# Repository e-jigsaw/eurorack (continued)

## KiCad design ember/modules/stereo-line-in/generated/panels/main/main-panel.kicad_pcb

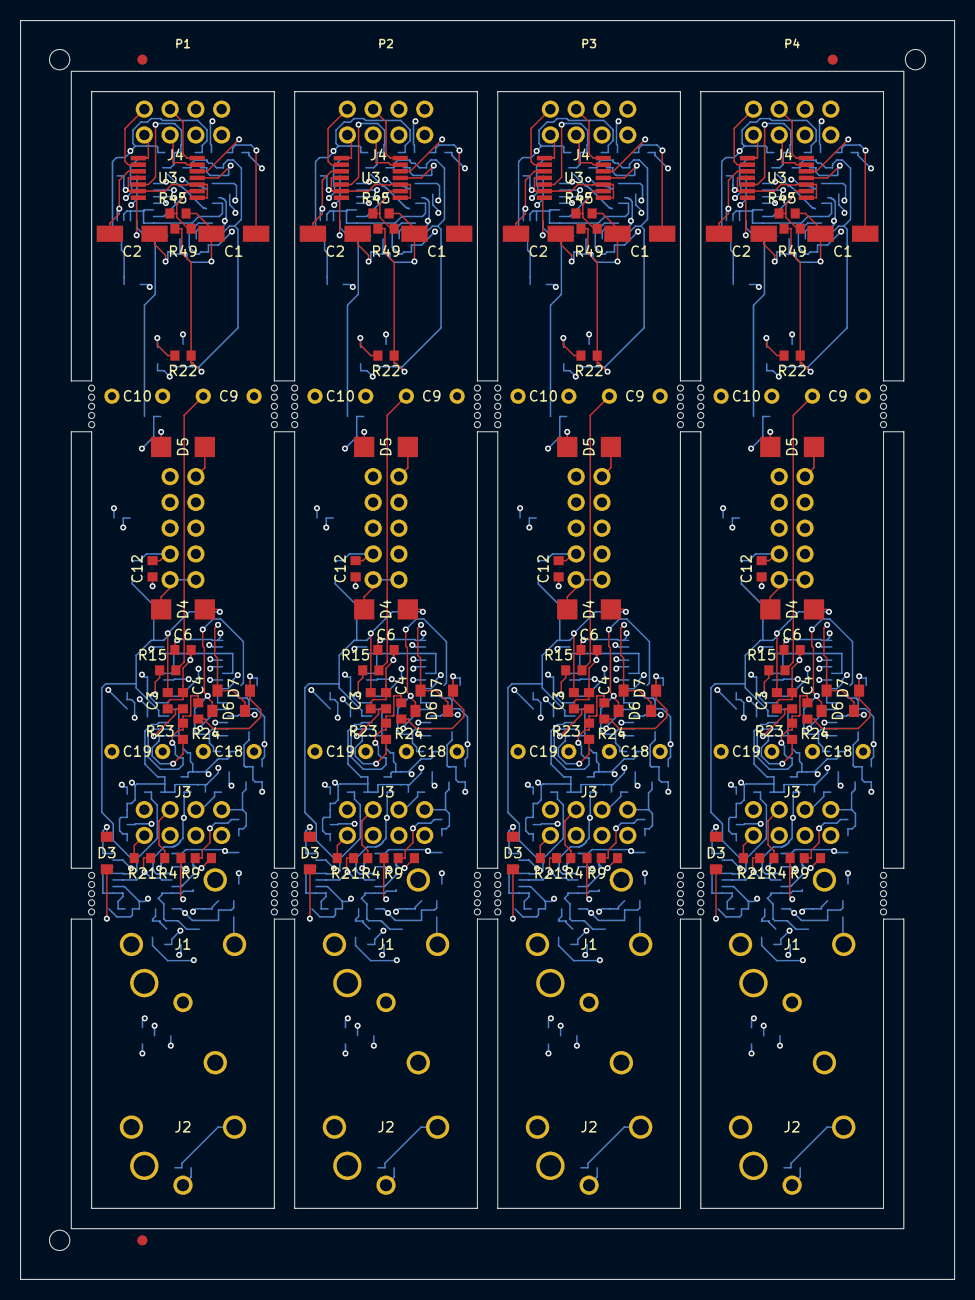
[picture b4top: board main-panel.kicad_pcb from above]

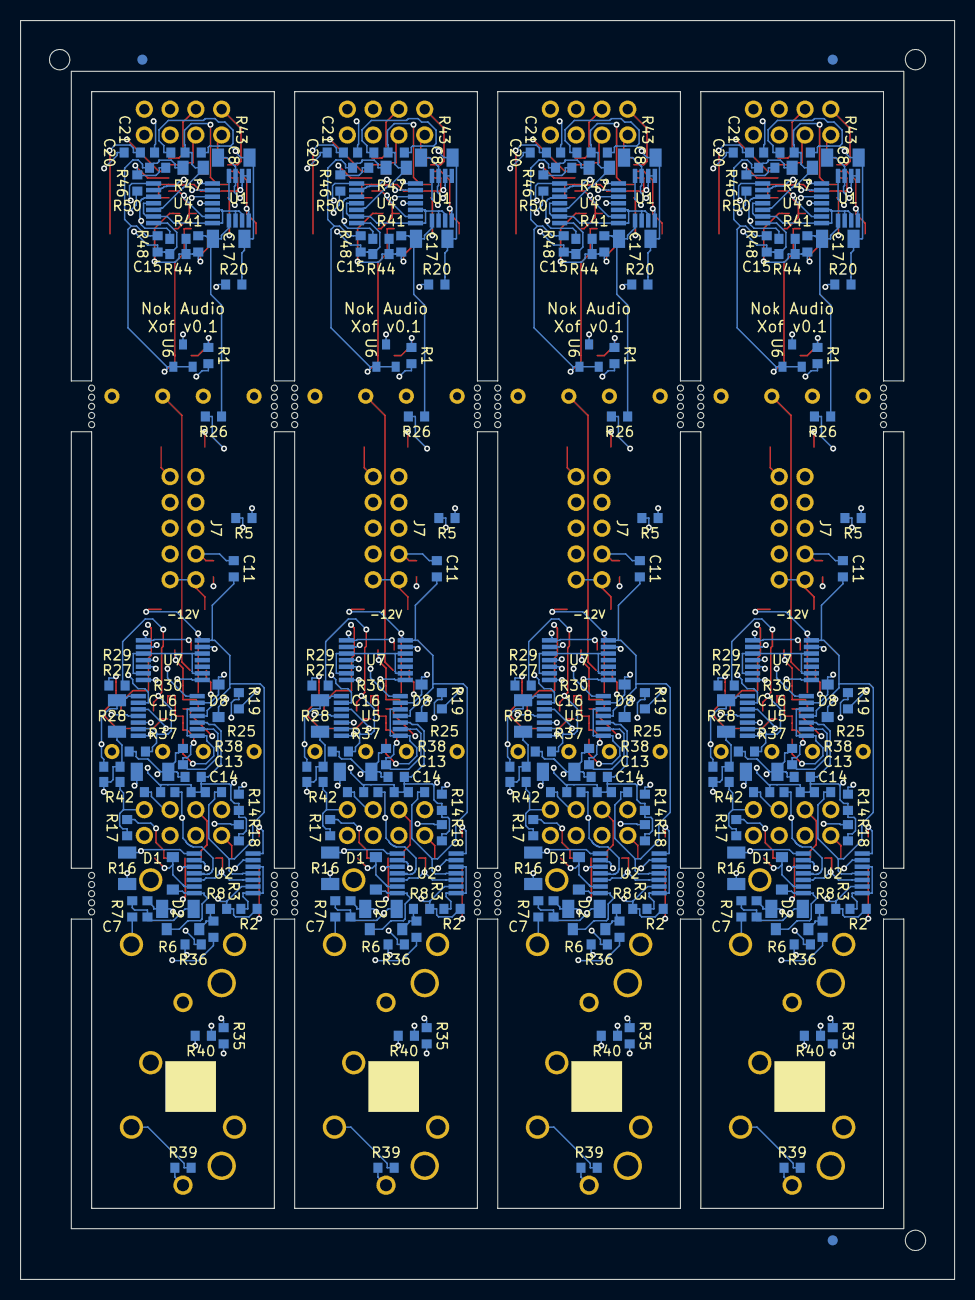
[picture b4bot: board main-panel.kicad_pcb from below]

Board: 4 copper layers, 92.0 x 124.0 mm, 417 parts (215 on the bottom side), 236 nets.

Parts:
FIDB1, FIDB2, FIDB3: Panel_Fiducial
FIDF1, FIDF2, FIDF3: Panel_Fiducial
MB1, MB2, MB3, MB4, MB5, MB6, MB7, MB8, MB9, MB10, MB11, MB12, MB13, MB14, MB15, MB16, MB17, MB18, MB19, MB20, MB21, MB22, MB23, MB24, MB25, MB26, MB27, MB28, MB29, MB30, MB31, MB32, MB33, MB34, MB35, MB36, MB37, MB38, MB39, MB40, MB41, MB42, MB43, MB44, MB45, MB46, MB47, MB48, MB49, MB50, MB51, MB52, MB53, MB54, MB55, MB56, MB57, MB58, MB59, MB60, MB61, MB62, MB63, MB64, MB65, MB66, MB67, MB68, MB69, MB70, MB71, MB72, MB73, MB74, MB75, MB76, MB77, MB78, MB79, MB80: Panel_NPTH
P1_C_BULK_N, P1_C_BULK_P, P2_C_BULK_N, P2_C_BULK_P, P3_C_BULK_N, P3_C_BULK_P, P4_C_BULK_N, P4_C_BULK_P: RVT1E220M0505; SMD,D5xL5.4mm
P1_C_ENV_N, P1_C_ENV_P, P1_C_L_CMP, P1_C_L_VN, P1_C_L_VP, P1_C_RX_N, P1_C_RX_P, P1_C_R_CMP, P1_C_R_VN, P1_C_R_VP, P2_C_ENV_N, P2_C_ENV_P, P2_C_L_CMP, P2_C_L_VN, P2_C_L_VP, P2_C_RX_N, P2_C_RX_P, P2_C_R_CMP, P2_C_R_VN, P2_C_R_VP, P3_C_ENV_N, P3_C_ENV_P, P3_C_L_CMP, P3_C_L_VN, P3_C_L_VP, P3_C_RX_N, P3_C_RX_P, P3_C_R_CMP, P3_C_R_VN, P3_C_R_VP, P4_C_ENV_N, P4_C_ENV_P, P4_C_L_CMP, P4_C_L_VN, P4_C_L_VP, P4_C_RX_N, P4_C_RX_P, P4_C_R_CMP, P4_C_R_VN, P4_C_R_VP: CC0603KRX7R9BB104; 0603
P1_C_L_GAIN_F, P1_C_R_GAIN_F, P2_C_L_GAIN_F, P2_C_R_GAIN_F, P3_C_L_GAIN_F, P3_C_R_GAIN_F, P4_C_L_GAIN_F, P4_C_R_GAIN_F: CL10C100JB8NNNC; 0603
P1_C_L_HOLD, P1_C_R_HOLD, P2_C_L_HOLD, P2_C_R_HOLD, P3_C_L_HOLD, P3_C_R_HOLD, P4_C_L_HOLD, P4_C_R_HOLD: GRM31C5C1H104JA01L; 1206
P1_C_L_N_AC, P1_C_L_P_AC, P1_C_R_N_AC, P1_C_R_P_AC, P2_C_L_N_AC, P2_C_L_P_AC, P2_C_R_N_AC, P2_C_R_P_AC, P3_C_L_N_AC, P3_C_L_P_AC, P3_C_R_N_AC, P3_C_R_P_AC, P4_C_L_N_AC, P4_C_L_P_AC, P4_C_R_N_AC, P4_C_R_P_AC: MKS2C041001F00JSSD; WIMA
P1_D_L_HALF_CLAMP, P1_D_L_HALF_RECT, P1_D_L_PEAK, P1_D_R_HALF_CLAMP, P1_D_R_HALF_RECT, P1_D_R_PEAK, P2_D_L_HALF_CLAMP, P2_D_L_HALF_RECT, P2_D_L_PEAK, P2_D_R_HALF_CLAMP, P2_D_R_HALF_RECT, P2_D_R_PEAK, P3_D_L_HALF_CLAMP, P3_D_L_HALF_RECT, P3_D_L_PEAK, P3_D_R_HALF_CLAMP, P3_D_R_HALF_RECT, P3_D_R_PEAK, P4_D_L_HALF_CLAMP, P4_D_L_HALF_RECT, P4_D_L_PEAK, P4_D_R_HALF_CLAMP, P4_D_R_HALF_RECT, P4_D_R_PEAK: 1N4148W; SOD-123
P1_D_PWR_N, P1_D_PWR_P, P2_D_PWR_N, P2_D_PWR_P, P3_D_PWR_N, P3_D_PWR_P, P4_D_PWR_N, P4_D_PWR_P: SS14; SMA(DO-214AC)
P1_J_IN_L, P1_J_IN_R, P2_J_IN_L, P2_J_IN_R, P3_J_IN_L, P3_J_IN_R, P4_J_IN_L, P4_J_IN_R: NJ3FD-V
P1_J_LINK_BOTTOM, P1_J_LINK_TOP, P2_J_LINK_BOTTOM, P2_J_LINK_TOP, P3_J_LINK_BOTTOM, P3_J_LINK_TOP, P4_J_LINK_BOTTOM, P4_J_LINK_TOP: SSW-104-01-F-D; SSW-2x4
P1_J_PWR, P2_J_PWR, P3_J_PWR, P4_J_PWR: DC3-2.54-10PAS; DC3
P1_R_LED_SUPPLY, P2_R_LED_SUPPLY, P3_R_LED_SUPPLY, P4_R_LED_SUPPLY: 0603WAF470JT5E; 0603
P1_R_L_ABS_FB, P1_R_R_ABS_FB, P2_R_L_ABS_FB, P2_R_R_ABS_FB, P3_R_L_ABS_FB, P3_R_R_ABS_FB, P4_R_L_ABS_FB, P4_R_R_ABS_FB: RT0603BRD0720KL; 0603
P1_R_L_ABS_HALF, P1_R_R_ABS_HALF, P2_R_L_ABS_HALF, P2_R_R_ABS_HALF, P3_R_L_ABS_HALF, P3_R_R_ABS_HALF, P4_R_L_ABS_HALF, P4_R_R_ABS_HALF: RT0603BRD0750KL; 0603
P1_R_L_ABS_RAW, P1_R_L_HALF_FB, P1_R_L_HALF_IN, P1_R_R_ABS_RAW, P1_R_R_HALF_FB, P1_R_R_HALF_IN, P2_R_L_ABS_RAW, P2_R_L_HALF_FB, P2_R_L_HALF_IN, P2_R_R_ABS_RAW, P2_R_R_HALF_FB, P2_R_R_HALF_IN, P3_R_L_ABS_RAW, P3_R_L_HALF_FB, P3_R_L_HALF_IN, P3_R_R_ABS_RAW, P3_R_R_HALF_FB, P3_R_R_HALF_IN, P4_R_L_ABS_RAW, P4_R_L_HALF_FB, P4_R_L_HALF_IN, P4_R_R_ABS_RAW, P4_R_R_HALF_FB, P4_R_R_HALF_IN: RT0603BRD07100KL; 0603
P1_R_L_ATTACK, P1_R_R_ATTACK, P2_R_L_ATTACK, P2_R_R_ATTACK, P3_R_L_ATTACK, P3_R_R_ATTACK, P4_R_L_ATTACK, P4_R_R_ATTACK: 0603WAF1001T5E; 0603
P1_R_L_GAIN_F, P1_R_R_GAIN_F, P2_R_L_GAIN_F, P2_R_R_GAIN_F, P3_R_L_GAIN_F, P3_R_R_GAIN_F, P4_R_L_GAIN_F, P4_R_R_GAIN_F: RT1206BRE0790KL; 1206
P1_R_L_GAIN_G, P1_R_R_GAIN_G, P1_R_TH_BOTTOM_1, P1_R_TH_BOTTOM_2, P1_R_TH_BOTTOM_3, P1_R_TH_BOTTOM_4, P2_R_L_GAIN_G, P2_R_R_GAIN_G, P2_R_TH_BOTTOM_1, P2_R_TH_BOTTOM_2, P2_R_TH_BOTTOM_3, P2_R_TH_BOTTOM_4, P3_R_L_GAIN_G, P3_R_R_GAIN_G, P3_R_TH_BOTTOM_1, P3_R_TH_BOTTOM_2, P3_R_TH_BOTTOM_3, P3_R_TH_BOTTOM_4, P4_R_L_GAIN_G, P4_R_R_GAIN_G, P4_R_TH_BOTTOM_1, P4_R_TH_BOTTOM_2, P4_R_TH_BOTTOM_3, P4_R_TH_BOTTOM_4: RT0603BRD0710KL; 0603
P1_R_L_N_BLEED, P1_R_L_OUT_BLEED, P1_R_L_P_BLEED, P1_R_L_RELEASE, P1_R_L_WIPER_FAIL, P1_R_R_N_BLEED, P1_R_R_OUT_BLEED, P1_R_R_P_BLEED, P1_R_R_RELEASE, P1_R_R_WIPER_FAIL, P2_R_L_N_BLEED, P2_R_L_OUT_BLEED, P2_R_L_P_BLEED, P2_R_L_RELEASE, P2_R_L_WIPER_FAIL, P2_R_R_N_BLEED, P2_R_R_OUT_BLEED, P2_R_R_P_BLEED, P2_R_R_RELEASE, P2_R_R_WIPER_FAIL, P3_R_L_N_BLEED, P3_R_L_OUT_BLEED, P3_R_L_P_BLEED, P3_R_L_RELEASE, P3_R_L_WIPER_FAIL, P3_R_R_N_BLEED, P3_R_R_OUT_BLEED, P3_R_R_P_BLEED, P3_R_R_RELEASE, P3_R_R_WIPER_FAIL, P4_R_L_N_BLEED, P4_R_L_OUT_BLEED, P4_R_L_P_BLEED, P4_R_L_RELEASE, P4_R_L_WIPER_FAIL, P4_R_R_N_BLEED, P4_R_R_OUT_BLEED, P4_R_R_P_BLEED, P4_R_R_RELEASE, P4_R_R_WIPER_FAIL: 0603WAF1004T5E; 0603
P1_R_L_N_SERIES, P1_R_L_P_SERIES, P1_R_R_N_SERIES, P1_R_R_P_SERIES, P2_R_L_N_SERIES, P2_R_L_P_SERIES, P2_R_R_N_SERIES, P2_R_R_P_SERIES, P3_R_L_N_SERIES, P3_R_L_P_SERIES, P3_R_R_N_SERIES, P3_R_R_P_SERIES, P4_R_L_N_SERIES, P4_R_L_P_SERIES, P4_R_R_N_SERIES, P4_R_R_P_SERIES: RT0603BRD071KL; 0603
P1_R_L_OUT, P1_R_R_OUT, P2_R_L_OUT, P2_R_R_OUT, P3_R_L_OUT, P3_R_R_OUT, P4_R_L_OUT, P4_R_R_OUT: HP06W2F1000T5E; 1206
P1_R_REFERENCE, P2_R_REFERENCE, P3_R_REFERENCE, P4_R_REFERENCE: 0603WAF2201T5E; 0603
P1_R_TH_TOP_1, P2_R_TH_TOP_1, P3_R_TH_TOP_1, P4_R_TH_TOP_1: RT0805BRD07240KL; 0805
P1_R_TH_TOP_2, P2_R_TH_TOP_2, P3_R_TH_TOP_2, P4_R_TH_TOP_2: RT0603BRD0752K3L; 0603
P1_R_TH_TOP_3, P2_R_TH_TOP_3, P3_R_TH_TOP_3, P4_R_TH_TOP_3: RT0603BRD0715KL; 0603
P1_R_TH_TOP_4, P2_R_TH_TOP_4, P3_R_TH_TOP_4, P4_R_TH_TOP_4: RT0603BRD075K62L; 0603
P1_U_ENV, P2_U_ENV, P3_U_ENV, P4_U_ENV: OPA1678IDGKR; VSSOP-8
P1_U_L, P1_U_R, P2_U_L, P2_U_R, P3_U_L, P3_U_R, P4_U_L, P4_U_R: OPA1679IPWR; TSSOP-14
P1_U_METER_L, P1_U_METER_R, P2_U_METER_L, P2_U_METER_R, P3_U_METER_L, P3_U_METER_R, P4_U_METER_L, P4_U_METER_R: LM339BIPWR; TSSOP-14
P1_U_REF, P2_U_REF, P3_U_REF, P4_U_REF: TL431BIDBZR; SOT-23-3
P1_U_RX, P2_U_RX, P3_U_RX, P4_U_RX: INA1650IPWR; TSSOP-14
TOOL1, TOOL2, TOOL3: Panel_NPTH

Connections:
P1_GND: P1_C_BULK_N.1, P1_C_BULK_P.2, P1_C_ENV_N.1, P1_C_ENV_P.2, P1_C_L_CMP.2, P1_C_L_HOLD.2, P1_C_L_VN.1, P1_C_L_VP.2, P1_C_RX_N.1, P1_C_RX_P.2, P1_C_R_CMP.2, P1_C_R_HOLD.2, P1_C_R_VN.1, P1_C_R_VP.2, P1_J_IN_L.3, P1_J_IN_R.3, P1_J_LINK_BOTTOM.7, P1_J_PWR.3, P1_J_PWR.4, P1_J_PWR.5, P1_J_PWR.6, P1_J_PWR.7, P1_J_PWR.8, P1_R_L_GAIN_G.2, P1_R_L_N_BLEED.2, P1_R_L_OUT_BLEED.2, P1_R_L_P_BLEED.2, P1_R_L_RELEASE.2, P1_R_L_WIPER_FAIL.2, P1_R_R_GAIN_G.2, P1_R_R_N_BLEED.2, P1_R_R_OUT_BLEED.2, P1_R_R_P_BLEED.2, P1_R_R_RELEASE.2, P1_R_R_WIPER_FAIL.2, P1_R_TH_BOTTOM_1.2, P1_R_TH_BOTTOM_2.2, P1_R_TH_BOTTOM_3.2, P1_R_TH_BOTTOM_4.2, P1_U_L.5, P1_U_L.10, P1_U_METER_L.12, P1_U_METER_R.12, P1_U_R.5, P1_U_R.10, P1_U_REF.3, P1_U_RX.3, P1_U_RX.6, P1_U_RX.9, P1_U_RX.12
P1_L_ABS: P1_R_L_ABS_FB.1, P1_U_L.8, P1_U_L.12
P1_L_ABS_SUM: P1_R_L_ABS_FB.2, P1_R_L_ABS_HALF.2, P1_R_L_ABS_RAW.2, P1_U_L.9
P1_L_DRIVE: P1_C_L_GAIN_F.1, P1_R_L_GAIN_F.1, P1_R_L_OUT.1, P1_U_L.1
P1_L_ENV: P1_C_L_HOLD.1, P1_R_L_ATTACK.2, P1_R_L_RELEASE.1, P1_U_ENV.3
P1_L_ENV_BUF: P1_U_ENV.1, P1_U_ENV.2, P1_U_METER_L.4, P1_U_METER_L.6, P1_U_METER_L.8, P1_U_METER_L.10
P1_L_GAIN_FB: P1_C_L_GAIN_F.2, P1_R_L_GAIN_F.2, P1_R_L_GAIN_G.1, P1_U_L.2
P1_L_HALF: P1_D_L_HALF_RECT.2, P1_R_L_ABS_HALF.1, P1_R_L_HALF_FB.1
P1_L_HALF_DRIVE: P1_D_L_HALF_CLAMP.2, P1_D_L_HALF_RECT.1, P1_U_L.7
P1_L_HALF_SUM: P1_D_L_HALF_CLAMP.1, P1_R_L_HALF_FB.2, P1_R_L_HALF_IN.2, P1_U_L.6
P1_L_LED_1_K: P1_J_LINK_TOP.1, P1_U_METER_L.2
P1_L_LED_2_K: P1_J_LINK_TOP.2, P1_U_METER_L.1
P1_L_LED_3_K: P1_J_LINK_TOP.3, P1_U_METER_L.14
P1_L_LED_4_K: P1_J_LINK_TOP.4, P1_U_METER_L.13
P1_L_N_SERIES: P1_C_L_N_AC.1, P1_R_L_N_SERIES.2
P1_L_OUT: P1_J_LINK_BOTTOM.3, P1_R_L_ABS_RAW.1, P1_R_L_HALF_IN.1, P1_R_L_OUT.2, P1_R_L_OUT_BLEED.1
P1_L_PEAK_DRIVE: P1_D_L_PEAK.2, P1_U_L.14
P1_L_PEAK_FOLLOW: P1_D_L_PEAK.1, P1_R_L_ATTACK.1, P1_U_L.13
P1_L_P_SERIES: P1_C_L_P_AC.1, P1_R_L_P_SERIES.2
P1_L_RING: P1_J_IN_L.2, P1_R_L_N_BLEED.1, P1_R_L_N_SERIES.1
P1_L_RX_N: P1_C_L_N_AC.2, P1_U_RX.4
P1_L_RX_OUT: P1_J_LINK_BOTTOM.1, P1_U_RX.13
P1_L_RX_P: P1_C_L_P_AC.2, P1_U_RX.2
P1_L_TIP: P1_J_IN_L.1, P1_R_L_P_BLEED.1, P1_R_L_P_SERIES.1
P1_L_WIPER: P1_J_LINK_BOTTOM.2, P1_R_L_WIPER_FAIL.1, P1_U_L.3
P1_R_ABS: P1_R_R_ABS_FB.1, P1_U_R.8, P1_U_R.12
P1_R_ABS_SUM: P1_R_R_ABS_FB.2, P1_R_R_ABS_HALF.2, P1_R_R_ABS_RAW.2, P1_U_R.9
P1_R_DRIVE: P1_C_R_GAIN_F.1, P1_R_R_GAIN_F.1, P1_R_R_OUT.1, P1_U_R.1
P1_R_ENV: P1_C_R_HOLD.1, P1_R_R_ATTACK.2, P1_R_R_RELEASE.1, P1_U_ENV.5
P1_R_ENV_BUF: P1_U_ENV.6, P1_U_ENV.7, P1_U_METER_R.4, P1_U_METER_R.6, P1_U_METER_R.8, P1_U_METER_R.10
P1_R_GAIN_FB: P1_C_R_GAIN_F.2, P1_R_R_GAIN_F.2, P1_R_R_GAIN_G.1, P1_U_R.2
P1_R_HALF: P1_D_R_HALF_RECT.2, P1_R_R_ABS_HALF.1, P1_R_R_HALF_FB.1
P1_R_HALF_DRIVE: P1_D_R_HALF_CLAMP.2, P1_D_R_HALF_RECT.1, P1_U_R.7
P1_R_HALF_SUM: P1_D_R_HALF_CLAMP.1, P1_R_R_HALF_FB.2, P1_R_R_HALF_IN.2, P1_U_R.6
P1_R_LED_1_K: P1_J_LINK_TOP.5, P1_U_METER_R.2
P1_R_LED_2_K: P1_J_LINK_TOP.6, P1_U_METER_R.1
P1_R_LED_3_K: P1_J_LINK_TOP.7, P1_U_METER_R.14
P1_R_LED_4_K: P1_J_LINK_TOP.8, P1_U_METER_R.13
P1_R_N_SERIES: P1_C_R_N_AC.1, P1_R_R_N_SERIES.2
P1_R_OUT: P1_J_LINK_BOTTOM.6, P1_R_R_ABS_RAW.1, P1_R_R_HALF_IN.1, P1_R_R_OUT.2, P1_R_R_OUT_BLEED.1
P1_R_PEAK_DRIVE: P1_D_R_PEAK.2, P1_U_R.14
P1_R_PEAK_FOLLOW: P1_D_R_PEAK.1, P1_R_R_ATTACK.1, P1_U_R.13
P1_R_P_SERIES: P1_C_R_P_AC.1, P1_R_R_P_SERIES.2
P1_R_RING: P1_J_IN_R.2, P1_R_R_N_BLEED.1, P1_R_R_N_SERIES.1
P1_R_RX_N: P1_C_R_N_AC.2, P1_U_RX.5
P1_R_RX_OUT: P1_J_LINK_BOTTOM.4, P1_U_RX.8
P1_R_RX_P: P1_C_R_P_AC.2, P1_U_RX.7
P1_R_TIP: P1_J_IN_R.1, P1_R_R_P_BLEED.1, P1_R_R_P_SERIES.1
P1_R_WIPER: P1_J_LINK_BOTTOM.5, P1_R_R_WIPER_FAIL.1, P1_U_R.3
P1_TH_1: P1_R_TH_BOTTOM_1.1, P1_R_TH_TOP_1.2, P1_U_METER_L.5, P1_U_METER_R.5
P1_TH_2: P1_R_TH_BOTTOM_2.1, P1_R_TH_TOP_2.2, P1_U_METER_L.7, P1_U_METER_R.7
P1_TH_3: P1_R_TH_BOTTOM_3.1, P1_R_TH_TOP_3.2, P1_U_METER_L.9, P1_U_METER_R.9
P1_TH_4: P1_R_TH_BOTTOM_4.1, P1_R_TH_TOP_4.2, P1_U_METER_L.11, P1_U_METER_R.11
P1_VLED: P1_J_LINK_BOTTOM.8, P1_R_LED_SUPPLY.2
P1_VN: P1_C_BULK_N.2, P1_C_ENV_N.2, P1_C_L_VN.2, P1_C_RX_N.2, P1_C_R_VN.2, P1_D_PWR_N.2, P1_U_ENV.4, P1_U_L.11, P1_U_R.11, P1_U_RX.14
P1_VN_RAW: P1_D_PWR_N.1, P1_J_PWR.1, P1_J_PWR.2
P1_VP: P1_C_BULK_P.1, P1_C_ENV_P.1, P1_C_L_CMP.1, P1_C_L_VP.1, P1_C_RX_P.1, P1_C_R_CMP.1, P1_C_R_VP.1, P1_D_PWR_P.1, P1_R_LED_SUPPLY.1, P1_R_REFERENCE.1, P1_U_ENV.8, P1_U_L.4, P1_U_METER_L.3, P1_U_METER_R.3, P1_U_R.4, P1_U_RX.1
P1_VP_RAW: P1_D_PWR_P.2, P1_J_PWR.9, P1_J_PWR.10
P1_VREF: P1_R_REFERENCE.2, P1_R_TH_TOP_1.1, P1_R_TH_TOP_2.1, P1_R_TH_TOP_3.1, P1_R_TH_TOP_4.1, P1_U_REF.1, P1_U_REF.2
P2_GND: P2_C_BULK_N.1, P2_C_BULK_P.2, P2_C_ENV_N.1, P2_C_ENV_P.2, P2_C_L_CMP.2, P2_C_L_HOLD.2, P2_C_L_VN.1, P2_C_L_VP.2, P2_C_RX_N.1, P2_C_RX_P.2, P2_C_R_CMP.2, P2_C_R_HOLD.2, P2_C_R_VN.1, P2_C_R_VP.2, P2_J_IN_L.3, P2_J_IN_R.3, P2_J_LINK_BOTTOM.7, P2_J_PWR.3, P2_J_PWR.4, P2_J_PWR.5, P2_J_PWR.6, P2_J_PWR.7, P2_J_PWR.8, P2_R_L_GAIN_G.2, P2_R_L_N_BLEED.2, P2_R_L_OUT_BLEED.2, P2_R_L_P_BLEED.2, P2_R_L_RELEASE.2, P2_R_L_WIPER_FAIL.2, P2_R_R_GAIN_G.2, P2_R_R_N_BLEED.2, P2_R_R_OUT_BLEED.2, P2_R_R_P_BLEED.2, P2_R_R_RELEASE.2, P2_R_R_WIPER_FAIL.2, P2_R_TH_BOTTOM_1.2, P2_R_TH_BOTTOM_2.2, P2_R_TH_BOTTOM_3.2, P2_R_TH_BOTTOM_4.2, P2_U_L.5, P2_U_L.10, P2_U_METER_L.12, P2_U_METER_R.12, P2_U_R.5, P2_U_R.10, P2_U_REF.3, P2_U_RX.3, P2_U_RX.6, P2_U_RX.9, P2_U_RX.12
P2_L_ABS: P2_R_L_ABS_FB.1, P2_U_L.8, P2_U_L.12
P2_L_ABS_SUM: P2_R_L_ABS_FB.2, P2_R_L_ABS_HALF.2, P2_R_L_ABS_RAW.2, P2_U_L.9
P2_L_DRIVE: P2_C_L_GAIN_F.1, P2_R_L_GAIN_F.1, P2_R_L_OUT.1, P2_U_L.1
P2_L_ENV: P2_C_L_HOLD.1, P2_R_L_ATTACK.2, P2_R_L_RELEASE.1, P2_U_ENV.3
P2_L_ENV_BUF: P2_U_ENV.1, P2_U_ENV.2, P2_U_METER_L.4, P2_U_METER_L.6, P2_U_METER_L.8, P2_U_METER_L.10
P2_L_GAIN_FB: P2_C_L_GAIN_F.2, P2_R_L_GAIN_F.2, P2_R_L_GAIN_G.1, P2_U_L.2
P2_L_HALF: P2_D_L_HALF_RECT.2, P2_R_L_ABS_HALF.1, P2_R_L_HALF_FB.1
P2_L_HALF_DRIVE: P2_D_L_HALF_CLAMP.2, P2_D_L_HALF_RECT.1, P2_U_L.7
P2_L_HALF_SUM: P2_D_L_HALF_CLAMP.1, P2_R_L_HALF_FB.2, P2_R_L_HALF_IN.2, P2_U_L.6
P2_L_LED_1_K: P2_J_LINK_TOP.1, P2_U_METER_L.2
P2_L_LED_2_K: P2_J_LINK_TOP.2, P2_U_METER_L.1
P2_L_LED_3_K: P2_J_LINK_TOP.3, P2_U_METER_L.14
P2_L_LED_4_K: P2_J_LINK_TOP.4, P2_U_METER_L.13
P2_L_N_SERIES: P2_C_L_N_AC.1, P2_R_L_N_SERIES.2
P2_L_OUT: P2_J_LINK_BOTTOM.3, P2_R_L_ABS_RAW.1, P2_R_L_HALF_IN.1, P2_R_L_OUT.2, P2_R_L_OUT_BLEED.1
P2_L_PEAK_DRIVE: P2_D_L_PEAK.2, P2_U_L.14
P2_L_PEAK_FOLLOW: P2_D_L_PEAK.1, P2_R_L_ATTACK.1, P2_U_L.13
P2_L_P_SERIES: P2_C_L_P_AC.1, P2_R_L_P_SERIES.2
P2_L_RING: P2_J_IN_L.2, P2_R_L_N_BLEED.1, P2_R_L_N_SERIES.1
P2_L_RX_N: P2_C_L_N_AC.2, P2_U_RX.4
P2_L_RX_OUT: P2_J_LINK_BOTTOM.1, P2_U_RX.13
P2_L_RX_P: P2_C_L_P_AC.2, P2_U_RX.2
P2_L_TIP: P2_J_IN_L.1, P2_R_L_P_BLEED.1, P2_R_L_P_SERIES.1
P2_L_WIPER: P2_J_LINK_BOTTOM.2, P2_R_L_WIPER_FAIL.1, P2_U_L.3
P2_R_ABS: P2_R_R_ABS_FB.1, P2_U_R.8, P2_U_R.12
P2_R_ABS_SUM: P2_R_R_ABS_FB.2, P2_R_R_ABS_HALF.2, P2_R_R_ABS_RAW.2, P2_U_R.9
P2_R_DRIVE: P2_C_R_GAIN_F.1, P2_R_R_GAIN_F.1, P2_R_R_OUT.1, P2_U_R.1
P2_R_ENV: P2_C_R_HOLD.1, P2_R_R_ATTACK.2, P2_R_R_RELEASE.1, P2_U_ENV.5
P2_R_ENV_BUF: P2_U_ENV.6, P2_U_ENV.7, P2_U_METER_R.4, P2_U_METER_R.6, P2_U_METER_R.8, P2_U_METER_R.10
P2_R_GAIN_FB: P2_C_R_GAIN_F.2, P2_R_R_GAIN_F.2, P2_R_R_GAIN_G.1, P2_U_R.2
P2_R_HALF: P2_D_R_HALF_RECT.2, P2_R_R_ABS_HALF.1, P2_R_R_HALF_FB.1
P2_R_HALF_DRIVE: P2_D_R_HALF_CLAMP.2, P2_D_R_HALF_RECT.1, P2_U_R.7
P2_R_HALF_SUM: P2_D_R_HALF_CLAMP.1, P2_R_R_HALF_FB.2, P2_R_R_HALF_IN.2, P2_U_R.6
P2_R_LED_1_K: P2_J_LINK_TOP.5, P2_U_METER_R.2
P2_R_LED_2_K: P2_J_LINK_TOP.6, P2_U_METER_R.1
P2_R_LED_3_K: P2_J_LINK_TOP.7, P2_U_METER_R.14
P2_R_LED_4_K: P2_J_LINK_TOP.8, P2_U_METER_R.13
P2_R_N_SERIES: P2_C_R_N_AC.1, P2_R_R_N_SERIES.2
P2_R_OUT: P2_J_LINK_BOTTOM.6, P2_R_R_ABS_RAW.1, P2_R_R_HALF_IN.1, P2_R_R_OUT.2, P2_R_R_OUT_BLEED.1
P2_R_PEAK_DRIVE: P2_D_R_PEAK.2, P2_U_R.14
P2_R_PEAK_FOLLOW: P2_D_R_PEAK.1, P2_R_R_ATTACK.1, P2_U_R.13
P2_R_P_SERIES: P2_C_R_P_AC.1, P2_R_R_P_SERIES.2
P2_R_RING: P2_J_IN_R.2, P2_R_R_N_BLEED.1, P2_R_R_N_SERIES.1
P2_R_RX_N: P2_C_R_N_AC.2, P2_U_RX.5
P2_R_RX_OUT: P2_J_LINK_BOTTOM.4, P2_U_RX.8
P2_R_RX_P: P2_C_R_P_AC.2, P2_U_RX.7
P2_R_TIP: P2_J_IN_R.1, P2_R_R_P_BLEED.1, P2_R_R_P_SERIES.1
P2_R_WIPER: P2_J_LINK_BOTTOM.5, P2_R_R_WIPER_FAIL.1, P2_U_R.3
P2_TH_1: P2_R_TH_BOTTOM_1.1, P2_R_TH_TOP_1.2, P2_U_METER_L.5, P2_U_METER_R.5
P2_TH_2: P2_R_TH_BOTTOM_2.1, P2_R_TH_TOP_2.2, P2_U_METER_L.7, P2_U_METER_R.7
P2_TH_3: P2_R_TH_BOTTOM_3.1, P2_R_TH_TOP_3.2, P2_U_METER_L.9, P2_U_METER_R.9
P2_TH_4: P2_R_TH_BOTTOM_4.1, P2_R_TH_TOP_4.2, P2_U_METER_L.11, P2_U_METER_R.11
P2_VLED: P2_J_LINK_BOTTOM.8, P2_R_LED_SUPPLY.2
P2_VN: P2_C_BULK_N.2, P2_C_ENV_N.2, P2_C_L_VN.2, P2_C_RX_N.2, P2_C_R_VN.2, P2_D_PWR_N.2, P2_U_ENV.4, P2_U_L.11, P2_U_R.11, P2_U_RX.14
P2_VN_RAW: P2_D_PWR_N.1, P2_J_PWR.1, P2_J_PWR.2
P2_VP: P2_C_BULK_P.1, P2_C_ENV_P.1, P2_C_L_CMP.1, P2_C_L_VP.1, P2_C_RX_P.1, P2_C_R_CMP.1, P2_C_R_VP.1, P2_D_PWR_P.1, P2_R_LED_SUPPLY.1, P2_R_REFERENCE.1, P2_U_ENV.8, P2_U_L.4, P2_U_METER_L.3, P2_U_METER_R.3, P2_U_R.4, P2_U_RX.1
P2_VP_RAW: P2_D_PWR_P.2, P2_J_PWR.9, P2_J_PWR.10
P2_VREF: P2_R_REFERENCE.2, P2_R_TH_TOP_1.1, P2_R_TH_TOP_2.1, P2_R_TH_TOP_3.1, P2_R_TH_TOP_4.1, P2_U_REF.1, P2_U_REF.2
P3_GND: P3_C_BULK_N.1, P3_C_BULK_P.2, P3_C_ENV_N.1, P3_C_ENV_P.2, P3_C_L_CMP.2, P3_C_L_HOLD.2, P3_C_L_VN.1, P3_C_L_VP.2, P3_C_RX_N.1, P3_C_RX_P.2, P3_C_R_CMP.2, P3_C_R_HOLD.2, P3_C_R_VN.1, P3_C_R_VP.2, P3_J_IN_L.3, P3_J_IN_R.3, P3_J_LINK_BOTTOM.7, P3_J_PWR.3, P3_J_PWR.4, P3_J_PWR.5, P3_J_PWR.6, P3_J_PWR.7, P3_J_PWR.8, P3_R_L_GAIN_G.2, P3_R_L_N_BLEED.2, P3_R_L_OUT_BLEED.2, P3_R_L_P_BLEED.2, P3_R_L_RELEASE.2, P3_R_L_WIPER_FAIL.2, P3_R_R_GAIN_G.2, P3_R_R_N_BLEED.2, P3_R_R_OUT_BLEED.2, P3_R_R_P_BLEED.2, P3_R_R_RELEASE.2, P3_R_R_WIPER_FAIL.2, P3_R_TH_BOTTOM_1.2, P3_R_TH_BOTTOM_2.2, P3_R_TH_BOTTOM_3.2, P3_R_TH_BOTTOM_4.2, P3_U_L.5, P3_U_L.10, P3_U_METER_L.12, P3_U_METER_R.12, P3_U_R.5, P3_U_R.10, P3_U_REF.3, P3_U_RX.3, P3_U_RX.6, P3_U_RX.9, P3_U_RX.12
P3_L_ABS: P3_R_L_ABS_FB.1, P3_U_L.8, P3_U_L.12
P3_L_ABS_SUM: P3_R_L_ABS_FB.2, P3_R_L_ABS_HALF.2, P3_R_L_ABS_RAW.2, P3_U_L.9
P3_L_DRIVE: P3_C_L_GAIN_F.1, P3_R_L_GAIN_F.1, P3_R_L_OUT.1, P3_U_L.1
P3_L_ENV: P3_C_L_HOLD.1, P3_R_L_ATTACK.2, P3_R_L_RELEASE.1, P3_U_ENV.3
P3_L_ENV_BUF: P3_U_ENV.1, P3_U_ENV.2, P3_U_METER_L.4, P3_U_METER_L.6, P3_U_METER_L.8, P3_U_METER_L.10
P3_L_GAIN_FB: P3_C_L_GAIN_F.2, P3_R_L_GAIN_F.2, P3_R_L_GAIN_G.1, P3_U_L.2
P3_L_HALF: P3_D_L_HALF_RECT.2, P3_R_L_ABS_HALF.1, P3_R_L_HALF_FB.1
P3_L_HALF_DRIVE: P3_D_L_HALF_CLAMP.2, P3_D_L_HALF_RECT.1, P3_U_L.7
P3_L_HALF_SUM: P3_D_L_HALF_CLAMP.1, P3_R_L_HALF_FB.2, P3_R_L_HALF_IN.2, P3_U_L.6
P3_L_LED_1_K: P3_J_LINK_TOP.1, P3_U_METER_L.2
P3_L_LED_2_K: P3_J_LINK_TOP.2, P3_U_METER_L.1
P3_L_LED_3_K: P3_J_LINK_TOP.3, P3_U_METER_L.14
P3_L_LED_4_K: P3_J_LINK_TOP.4, P3_U_METER_L.13
P3_L_N_SERIES: P3_C_L_N_AC.1, P3_R_L_N_SERIES.2
P3_L_OUT: P3_J_LINK_BOTTOM.3, P3_R_L_ABS_RAW.1, P3_R_L_HALF_IN.1, P3_R_L_OUT.2, P3_R_L_OUT_BLEED.1
P3_L_PEAK_DRIVE: P3_D_L_PEAK.2, P3_U_L.14
P3_L_PEAK_FOLLOW: P3_D_L_PEAK.1, P3_R_L_ATTACK.1, P3_U_L.13
P3_L_P_SERIES: P3_C_L_P_AC.1, P3_R_L_P_SERIES.2
P3_L_RING: P3_J_IN_L.2, P3_R_L_N_BLEED.1, P3_R_L_N_SERIES.1
P3_L_RX_N: P3_C_L_N_AC.2, P3_U_RX.4
P3_L_RX_OUT: P3_J_LINK_BOTTOM.1, P3_U_RX.13
P3_L_RX_P: P3_C_L_P_AC.2, P3_U_RX.2
P3_L_TIP: P3_J_IN_L.1, P3_R_L_P_BLEED.1, P3_R_L_P_SERIES.1
P3_L_WIPER: P3_J_LINK_BOTTOM.2, P3_R_L_WIPER_FAIL.1, P3_U_L.3
P3_R_ABS: P3_R_R_ABS_FB.1, P3_U_R.8, P3_U_R.12
P3_R_ABS_SUM: P3_R_R_ABS_FB.2, P3_R_R_ABS_HALF.2, P3_R_R_ABS_RAW.2, P3_U_R.9
P3_R_DRIVE: P3_C_R_GAIN_F.1, P3_R_R_GAIN_F.1, P3_R_R_OUT.1, P3_U_R.1
P3_R_ENV: P3_C_R_HOLD.1, P3_R_R_ATTACK.2, P3_R_R_RELEASE.1, P3_U_ENV.5
P3_R_ENV_BUF: P3_U_ENV.6, P3_U_ENV.7, P3_U_METER_R.4, P3_U_METER_R.6, P3_U_METER_R.8, P3_U_METER_R.10
P3_R_GAIN_FB: P3_C_R_GAIN_F.2, P3_R_R_GAIN_F.2, P3_R_R_GAIN_G.1, P3_U_R.2
P3_R_HALF: P3_D_R_HALF_RECT.2, P3_R_R_ABS_HALF.1, P3_R_R_HALF_FB.1
P3_R_HALF_DRIVE: P3_D_R_HALF_CLAMP.2, P3_D_R_HALF_RECT.1, P3_U_R.7
P3_R_HALF_SUM: P3_D_R_HALF_CLAMP.1, P3_R_R_HALF_FB.2, P3_R_R_HALF_IN.2, P3_U_R.6
P3_R_LED_1_K: P3_J_LINK_TOP.5, P3_U_METER_R.2
P3_R_LED_2_K: P3_J_LINK_TOP.6, P3_U_METER_R.1
P3_R_LED_3_K: P3_J_LINK_TOP.7, P3_U_METER_R.14
P3_R_LED_4_K: P3_J_LINK_TOP.8, P3_U_METER_R.13
P3_R_N_SERIES: P3_C_R_N_AC.1, P3_R_R_N_SERIES.2
P3_R_OUT: P3_J_LINK_BOTTOM.6, P3_R_R_ABS_RAW.1, P3_R_R_HALF_IN.1, P3_R_R_OUT.2, P3_R_R_OUT_BLEED.1
P3_R_PEAK_DRIVE: P3_D_R_PEAK.2, P3_U_R.14
P3_R_PEAK_FOLLOW: P3_D_R_PEAK.1, P3_R_R_ATTACK.1, P3_U_R.13
P3_R_P_SERIES: P3_C_R_P_AC.1, P3_R_R_P_SERIES.2
P3_R_RING: P3_J_IN_R.2, P3_R_R_N_BLEED.1, P3_R_R_N_SERIES.1
P3_R_RX_N: P3_C_R_N_AC.2, P3_U_RX.5
P3_R_RX_OUT: P3_J_LINK_BOTTOM.4, P3_U_RX.8
P3_R_RX_P: P3_C_R_P_AC.2, P3_U_RX.7
P3_R_TIP: P3_J_IN_R.1, P3_R_R_P_BLEED.1, P3_R_R_P_SERIES.1
P3_R_WIPER: P3_J_LINK_BOTTOM.5, P3_R_R_WIPER_FAIL.1, P3_U_R.3
P3_TH_1: P3_R_TH_BOTTOM_1.1, P3_R_TH_TOP_1.2, P3_U_METER_L.5, P3_U_METER_R.5
P3_TH_2: P3_R_TH_BOTTOM_2.1, P3_R_TH_TOP_2.2, P3_U_METER_L.7, P3_U_METER_R.7
P3_TH_3: P3_R_TH_BOTTOM_3.1, P3_R_TH_TOP_3.2, P3_U_METER_L.9, P3_U_METER_R.9
P3_TH_4: P3_R_TH_BOTTOM_4.1, P3_R_TH_TOP_4.2, P3_U_METER_L.11, P3_U_METER_R.11
P3_VLED: P3_J_LINK_BOTTOM.8, P3_R_LED_SUPPLY.2
P3_VN: P3_C_BULK_N.2, P3_C_ENV_N.2, P3_C_L_VN.2, P3_C_RX_N.2, P3_C_R_VN.2, P3_D_PWR_N.2, P3_U_ENV.4, P3_U_L.11, P3_U_R.11, P3_U_RX.14
P3_VN_RAW: P3_D_PWR_N.1, P3_J_PWR.1, P3_J_PWR.2
P3_VP: P3_C_BULK_P.1, P3_C_ENV_P.1, P3_C_L_CMP.1, P3_C_L_VP.1, P3_C_RX_P.1, P3_C_R_CMP.1, P3_C_R_VP.1, P3_D_PWR_P.1, P3_R_LED_SUPPLY.1, P3_R_REFERENCE.1, P3_U_ENV.8, P3_U_L.4, P3_U_METER_L.3, P3_U_METER_R.3, P3_U_R.4, P3_U_RX.1
P3_VP_RAW: P3_D_PWR_P.2, P3_J_PWR.9, P3_J_PWR.10
P3_VREF: P3_R_REFERENCE.2, P3_R_TH_TOP_1.1, P3_R_TH_TOP_2.1, P3_R_TH_TOP_3.1, P3_R_TH_TOP_4.1, P3_U_REF.1, P3_U_REF.2
P4_GND: P4_C_BULK_N.1, P4_C_BULK_P.2, P4_C_ENV_N.1, P4_C_ENV_P.2, P4_C_L_CMP.2, P4_C_L_HOLD.2, P4_C_L_VN.1, P4_C_L_VP.2, P4_C_RX_N.1, P4_C_RX_P.2, P4_C_R_CMP.2, P4_C_R_HOLD.2, P4_C_R_VN.1, P4_C_R_VP.2, P4_J_IN_L.3, P4_J_IN_R.3, P4_J_LINK_BOTTOM.7, P4_J_PWR.3, P4_J_PWR.4, P4_J_PWR.5, P4_J_PWR.6, P4_J_PWR.7, P4_J_PWR.8, P4_R_L_GAIN_G.2, P4_R_L_N_BLEED.2, P4_R_L_OUT_BLEED.2, P4_R_L_P_BLEED.2, P4_R_L_RELEASE.2, P4_R_L_WIPER_FAIL.2, P4_R_R_GAIN_G.2, P4_R_R_N_BLEED.2, P4_R_R_OUT_BLEED.2, P4_R_R_P_BLEED.2, P4_R_R_RELEASE.2, P4_R_R_WIPER_FAIL.2, P4_R_TH_BOTTOM_1.2, P4_R_TH_BOTTOM_2.2, P4_R_TH_BOTTOM_3.2, P4_R_TH_BOTTOM_4.2, P4_U_L.5, P4_U_L.10, P4_U_METER_L.12, P4_U_METER_R.12, P4_U_R.5, P4_U_R.10, P4_U_REF.3, P4_U_RX.3, P4_U_RX.6, P4_U_RX.9, P4_U_RX.12
P4_L_ABS: P4_R_L_ABS_FB.1, P4_U_L.8, P4_U_L.12
P4_L_ABS_SUM: P4_R_L_ABS_FB.2, P4_R_L_ABS_HALF.2, P4_R_L_ABS_RAW.2, P4_U_L.9
P4_L_DRIVE: P4_C_L_GAIN_F.1, P4_R_L_GAIN_F.1, P4_R_L_OUT.1, P4_U_L.1
P4_L_ENV: P4_C_L_HOLD.1, P4_R_L_ATTACK.2, P4_R_L_RELEASE.1, P4_U_ENV.3
P4_L_ENV_BUF: P4_U_ENV.1, P4_U_ENV.2, P4_U_METER_L.4, P4_U_METER_L.6, P4_U_METER_L.8, P4_U_METER_L.10
P4_L_GAIN_FB: P4_C_L_GAIN_F.2, P4_R_L_GAIN_F.2, P4_R_L_GAIN_G.1, P4_U_L.2
P4_L_HALF: P4_D_L_HALF_RECT.2, P4_R_L_ABS_HALF.1, P4_R_L_HALF_FB.1
P4_L_HALF_DRIVE: P4_D_L_HALF_CLAMP.2, P4_D_L_HALF_RECT.1, P4_U_L.7
P4_L_HALF_SUM: P4_D_L_HALF_CLAMP.1, P4_R_L_HALF_FB.2, P4_R_L_HALF_IN.2, P4_U_L.6
P4_L_LED_1_K: P4_J_LINK_TOP.1, P4_U_METER_L.2
P4_L_LED_2_K: P4_J_LINK_TOP.2, P4_U_METER_L.1
P4_L_LED_3_K: P4_J_LINK_TOP.3, P4_U_METER_L.14
P4_L_LED_4_K: P4_J_LINK_TOP.4, P4_U_METER_L.13
P4_L_N_SERIES: P4_C_L_N_AC.1, P4_R_L_N_SERIES.2
P4_L_OUT: P4_J_LINK_BOTTOM.3, P4_R_L_ABS_RAW.1, P4_R_L_HALF_IN.1, P4_R_L_OUT.2, P4_R_L_OUT_BLEED.1
P4_L_PEAK_DRIVE: P4_D_L_PEAK.2, P4_U_L.14
P4_L_PEAK_FOLLOW: P4_D_L_PEAK.1, P4_R_L_ATTACK.1, P4_U_L.13
P4_L_P_SERIES: P4_C_L_P_AC.1, P4_R_L_P_SERIES.2
P4_L_RING: P4_J_IN_L.2, P4_R_L_N_BLEED.1, P4_R_L_N_SERIES.1
P4_L_RX_N: P4_C_L_N_AC.2, P4_U_RX.4
P4_L_RX_OUT: P4_J_LINK_BOTTOM.1, P4_U_RX.13
P4_L_RX_P: P4_C_L_P_AC.2, P4_U_RX.2
P4_L_TIP: P4_J_IN_L.1, P4_R_L_P_BLEED.1, P4_R_L_P_SERIES.1
P4_L_WIPER: P4_J_LINK_BOTTOM.2, P4_R_L_WIPER_FAIL.1, P4_U_L.3
P4_R_ABS: P4_R_R_ABS_FB.1, P4_U_R.8, P4_U_R.12
P4_R_ABS_SUM: P4_R_R_ABS_FB.2, P4_R_R_ABS_HALF.2, P4_R_R_ABS_RAW.2, P4_U_R.9
P4_R_DRIVE: P4_C_R_GAIN_F.1, P4_R_R_GAIN_F.1, P4_R_R_OUT.1, P4_U_R.1
P4_R_ENV: P4_C_R_HOLD.1, P4_R_R_ATTACK.2, P4_R_R_RELEASE.1, P4_U_ENV.5
P4_R_ENV_BUF: P4_U_ENV.6, P4_U_ENV.7, P4_U_METER_R.4, P4_U_METER_R.6, P4_U_METER_R.8, P4_U_METER_R.10
P4_R_GAIN_FB: P4_C_R_GAIN_F.2, P4_R_R_GAIN_F.2, P4_R_R_GAIN_G.1, P4_U_R.2
P4_R_HALF: P4_D_R_HALF_RECT.2, P4_R_R_ABS_HALF.1, P4_R_R_HALF_FB.1
P4_R_HALF_DRIVE: P4_D_R_HALF_CLAMP.2, P4_D_R_HALF_RECT.1, P4_U_R.7
P4_R_HALF_SUM: P4_D_R_HALF_CLAMP.1, P4_R_R_HALF_FB.2, P4_R_R_HALF_IN.2, P4_U_R.6
P4_R_LED_1_K: P4_J_LINK_TOP.5, P4_U_METER_R.2
P4_R_LED_2_K: P4_J_LINK_TOP.6, P4_U_METER_R.1
P4_R_LED_3_K: P4_J_LINK_TOP.7, P4_U_METER_R.14
P4_R_LED_4_K: P4_J_LINK_TOP.8, P4_U_METER_R.13
P4_R_N_SERIES: P4_C_R_N_AC.1, P4_R_R_N_SERIES.2
P4_R_OUT: P4_J_LINK_BOTTOM.6, P4_R_R_ABS_RAW.1, P4_R_R_HALF_IN.1, P4_R_R_OUT.2, P4_R_R_OUT_BLEED.1
P4_R_PEAK_DRIVE: P4_D_R_PEAK.2, P4_U_R.14
P4_R_PEAK_FOLLOW: P4_D_R_PEAK.1, P4_R_R_ATTACK.1, P4_U_R.13
P4_R_P_SERIES: P4_C_R_P_AC.1, P4_R_R_P_SERIES.2
P4_R_RING: P4_J_IN_R.2, P4_R_R_N_BLEED.1, P4_R_R_N_SERIES.1
P4_R_RX_N: P4_C_R_N_AC.2, P4_U_RX.5
P4_R_RX_OUT: P4_J_LINK_BOTTOM.4, P4_U_RX.8
P4_R_RX_P: P4_C_R_P_AC.2, P4_U_RX.7
P4_R_TIP: P4_J_IN_R.1, P4_R_R_P_BLEED.1, P4_R_R_P_SERIES.1
P4_R_WIPER: P4_J_LINK_BOTTOM.5, P4_R_R_WIPER_FAIL.1, P4_U_R.3
P4_TH_1: P4_R_TH_BOTTOM_1.1, P4_R_TH_TOP_1.2, P4_U_METER_L.5, P4_U_METER_R.5
P4_TH_2: P4_R_TH_BOTTOM_2.1, P4_R_TH_TOP_2.2, P4_U_METER_L.7, P4_U_METER_R.7
P4_TH_3: P4_R_TH_BOTTOM_3.1, P4_R_TH_TOP_3.2, P4_U_METER_L.9, P4_U_METER_R.9
P4_TH_4: P4_R_TH_BOTTOM_4.1, P4_R_TH_TOP_4.2, P4_U_METER_L.11, P4_U_METER_R.11
P4_VLED: P4_J_LINK_BOTTOM.8, P4_R_LED_SUPPLY.2
P4_VN: P4_C_BULK_N.2, P4_C_ENV_N.2, P4_C_L_VN.2, P4_C_RX_N.2, P4_C_R_VN.2, P4_D_PWR_N.2, P4_U_ENV.4, P4_U_L.11, P4_U_R.11, P4_U_RX.14
P4_VN_RAW: P4_D_PWR_N.1, P4_J_PWR.1, P4_J_PWR.2
P4_VP: P4_C_BULK_P.1, P4_C_ENV_P.1, P4_C_L_CMP.1, P4_C_L_VP.1, P4_C_RX_P.1, P4_C_R_CMP.1, P4_C_R_VP.1, P4_D_PWR_P.1, P4_R_LED_SUPPLY.1, P4_R_REFERENCE.1, P4_U_ENV.8, P4_U_L.4, P4_U_METER_L.3, P4_U_METER_R.3, P4_U_R.4, P4_U_RX.1
P4_VP_RAW: P4_D_PWR_P.2, P4_J_PWR.9, P4_J_PWR.10
P4_VREF: P4_R_REFERENCE.2, P4_R_TH_TOP_1.1, P4_R_TH_TOP_2.1, P4_R_TH_TOP_3.1, P4_R_TH_TOP_4.1, P4_U_REF.1, P4_U_REF.2

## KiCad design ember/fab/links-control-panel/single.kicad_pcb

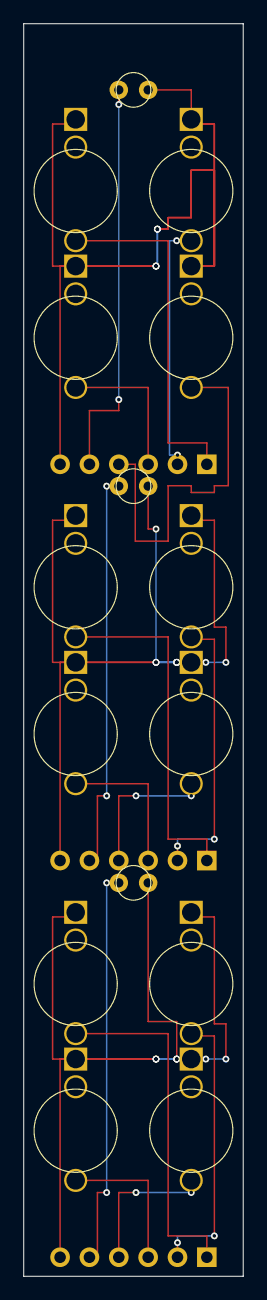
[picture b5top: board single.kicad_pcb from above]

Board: 2 copper layers, 19.0 x 108.4 mm, 18 parts (0 on the bottom side), 16 nets.

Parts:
HDR: HDR; pin_header_pinrow6_p2.54mm_id1mm_od1.7mm_male
HDR#2, HDR#3: HDR; pin_header_pinrow6_p2.54mm_id1mm_od1.7mm_male
J1, J2, J3, J4, J5, J6, J7, J8, J9, J10, J11, J12: PJ301M-12
LED1, LED2, LED3: LED; led

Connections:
.HDR > .LED to .LED1 > .anode: HDR.5, LED1.1
.HDR > .LED to .LED2 > .anode: HDR#2.5, LED2.1
.HDR > .LED to .LED3 > .anode: HDR#3.5, LED3.1
.HDR > .OUT to .J12 > .TIP: HDR#3.4, J12.1
.HDR > .OUT_A to .J2 > .TIP: HDR.2, J2.1
.HDR > .OUT_A to .J7 > .TIP: HDR#2.3, J7.1
.HDR > .OUT_B to .J3 > .TIP: HDR.3, J3.1
.HDR > .OUT_B to .J8 > .TIP: HDR#2.4, J8.1
.HDR > .OUT_C to .J4 > .TIP: HDR.4, J4.1
.J1 > .TIP to .HDR > .IN: HDR.1, J1.1
.J5 > .TIP to .HDR > .IN_A: HDR#2.1, J5.1
.J6 > .TIP to .HDR > .IN_B: HDR#2.2, J6.1
.J9 > .TIP to .HDR > .IN_A: HDR#3.1, J9.1
.J10 > .TIP to .HDR > .IN_B: HDR#3.2, J10.1
.J11 > .TIP to .HDR > .IN_C: HDR#3.3, J11.1
GND: HDR.6, HDR#2.6, HDR#3.6, J1.3, J2.3, J3.3, J4.3, J5.3, J6.3, J7.3, J8.3, J9.3, J10.3, J11.3, J12.3, LED1.2, LED2.2, LED3.2

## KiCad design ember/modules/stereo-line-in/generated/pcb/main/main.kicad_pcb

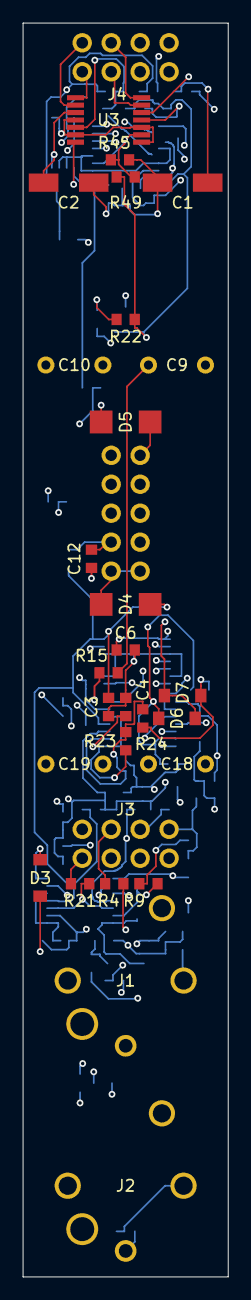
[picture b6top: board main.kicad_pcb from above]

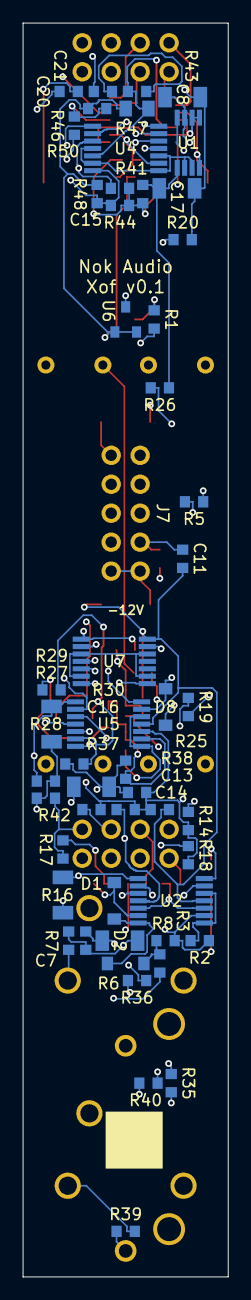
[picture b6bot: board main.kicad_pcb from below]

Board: 4 copper layers, 18.0 x 110.0 mm, 82 parts (53 on the bottom side), 59 nets.

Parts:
C_BULK_N: RVT1E220M0505; SMD,D5xL5.4mm
C_BULK_P: RVT1E220M0505; SMD,D5xL5.4mm
C_ENV_N: CC0603KRX7R9BB104; 0603
C_ENV_P: CC0603KRX7R9BB104; 0603
C_L_CMP: CC0603KRX7R9BB104; 0603
C_L_GAIN_F: CL10C100JB8NNNC; 0603
C_L_HOLD: GRM31C5C1H104JA01L; 1206
C_L_N_AC: MKS2C041001F00JSSD; WIMA
C_L_P_AC: MKS2C041001F00JSSD; WIMA
C_L_VN: CC0603KRX7R9BB104; 0603
C_L_VP: CC0603KRX7R9BB104; 0603
C_RX_N: CC0603KRX7R9BB104; 0603
C_RX_P: CC0603KRX7R9BB104; 0603
C_R_CMP: CC0603KRX7R9BB104; 0603
C_R_GAIN_F: CL10C100JB8NNNC; 0603
C_R_HOLD: GRM31C5C1H104JA01L; 1206
C_R_N_AC: MKS2C041001F00JSSD; WIMA
C_R_P_AC: MKS2C041001F00JSSD; WIMA
C_R_VN: CC0603KRX7R9BB104; 0603
C_R_VP: CC0603KRX7R9BB104; 0603
D_L_HALF_CLAMP: 1N4148W; SOD-123
D_L_HALF_RECT: 1N4148W; SOD-123
D_L_PEAK: 1N4148W; SOD-123
D_PWR_N: SS14; SMA(DO-214AC)
D_PWR_P: SS14; SMA(DO-214AC)
D_R_HALF_CLAMP: 1N4148W; SOD-123
D_R_HALF_RECT: 1N4148W; SOD-123
D_R_PEAK: 1N4148W; SOD-123
J_IN_L: NJ3FD-V
J_IN_R: NJ3FD-V
J_LINK_BOTTOM: SSW-104-01-F-D; SSW-2x4
J_LINK_TOP: SSW-104-01-F-D; SSW-2x4
J_PWR: DC3-2.54-10PAS; DC3
R_LED_SUPPLY: 0603WAF470JT5E; 0603
R_L_ABS_FB: RT0603BRD0720KL; 0603
R_L_ABS_HALF: RT0603BRD0750KL; 0603
R_L_ABS_RAW: RT0603BRD07100KL; 0603
R_L_ATTACK: 0603WAF1001T5E; 0603
R_L_GAIN_F: RT1206BRE0790KL; 1206
R_L_GAIN_G: RT0603BRD0710KL; 0603
R_L_HALF_FB: RT0603BRD07100KL; 0603
R_L_HALF_IN: RT0603BRD07100KL; 0603
R_L_N_BLEED: 0603WAF1004T5E; 0603
R_L_N_SERIES: RT0603BRD071KL; 0603
R_L_OUT: HP06W2F1000T5E; 1206
R_L_OUT_BLEED: 0603WAF1004T5E; 0603
R_L_P_BLEED: 0603WAF1004T5E; 0603
R_L_P_SERIES: RT0603BRD071KL; 0603
R_L_RELEASE: 0603WAF1004T5E; 0603
R_L_WIPER_FAIL: 0603WAF1004T5E; 0603
R_REFERENCE: 0603WAF2201T5E; 0603
R_R_ABS_FB: RT0603BRD0720KL; 0603
R_R_ABS_HALF: RT0603BRD0750KL; 0603
R_R_ABS_RAW: RT0603BRD07100KL; 0603
R_R_ATTACK: 0603WAF1001T5E; 0603
R_R_GAIN_F: RT1206BRE0790KL; 1206
R_R_GAIN_G: RT0603BRD0710KL; 0603
R_R_HALF_FB: RT0603BRD07100KL; 0603
R_R_HALF_IN: RT0603BRD07100KL; 0603
R_R_N_BLEED: 0603WAF1004T5E; 0603
R_R_N_SERIES: RT0603BRD071KL; 0603
R_R_OUT: HP06W2F1000T5E; 1206
R_R_OUT_BLEED: 0603WAF1004T5E; 0603
R_R_P_BLEED: 0603WAF1004T5E; 0603
R_R_P_SERIES: RT0603BRD071KL; 0603
R_R_RELEASE: 0603WAF1004T5E; 0603
R_R_WIPER_FAIL: 0603WAF1004T5E; 0603
R_TH_BOTTOM_1, R_TH_BOTTOM_2, R_TH_BOTTOM_3, R_TH_BOTTOM_4: RT0603BRD0710KL; 0603
R_TH_TOP_1: RT0805BRD07240KL; 0805
R_TH_TOP_2: RT0603BRD0752K3L; 0603
R_TH_TOP_3: RT0603BRD0715KL; 0603
R_TH_TOP_4: RT0603BRD075K62L; 0603
U_ENV: OPA1678IDGKR; VSSOP-8
U_L: OPA1679IPWR; TSSOP-14
U_METER_L: LM339BIPWR; TSSOP-14
U_METER_R: LM339BIPWR; TSSOP-14
U_R: OPA1679IPWR; TSSOP-14
U_REF: TL431BIDBZR; SOT-23-3
U_RX: INA1650IPWR; TSSOP-14

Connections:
GND: C_BULK_N.1, C_BULK_P.2, C_ENV_N.1, C_ENV_P.2, C_L_CMP.2, C_L_HOLD.2, C_L_VN.1, C_L_VP.2, C_RX_N.1, C_RX_P.2, C_R_CMP.2, C_R_HOLD.2, C_R_VN.1, C_R_VP.2, J_IN_L.3, J_IN_R.3, J_LINK_BOTTOM.7, J_PWR.3, J_PWR.4, J_PWR.5, J_PWR.6, J_PWR.7, J_PWR.8, R_L_GAIN_G.2, R_L_N_BLEED.2, R_L_OUT_BLEED.2, R_L_P_BLEED.2, R_L_RELEASE.2, R_L_WIPER_FAIL.2, R_R_GAIN_G.2, R_R_N_BLEED.2, R_R_OUT_BLEED.2, R_R_P_BLEED.2, R_R_RELEASE.2, R_R_WIPER_FAIL.2, R_TH_BOTTOM_1.2, R_TH_BOTTOM_2.2, R_TH_BOTTOM_3.2, R_TH_BOTTOM_4.2, U_L.5, U_L.10, U_METER_L.12, U_METER_R.12, U_R.5, U_R.10, U_REF.3, U_RX.3, U_RX.6, U_RX.9, U_RX.12
L_ABS: R_L_ABS_FB.1, U_L.8, U_L.12
L_ABS_SUM: R_L_ABS_FB.2, R_L_ABS_HALF.2, R_L_ABS_RAW.2, U_L.9
L_DRIVE: C_L_GAIN_F.1, R_L_GAIN_F.1, R_L_OUT.1, U_L.1
L_ENV: C_L_HOLD.1, R_L_ATTACK.2, R_L_RELEASE.1, U_ENV.3
L_ENV_BUF: U_ENV.1, U_ENV.2, U_METER_L.4, U_METER_L.6, U_METER_L.8, U_METER_L.10
L_GAIN_FB: C_L_GAIN_F.2, R_L_GAIN_F.2, R_L_GAIN_G.1, U_L.2
L_HALF: D_L_HALF_RECT.2, R_L_ABS_HALF.1, R_L_HALF_FB.1
L_HALF_DRIVE: D_L_HALF_CLAMP.2, D_L_HALF_RECT.1, U_L.7
L_HALF_SUM: D_L_HALF_CLAMP.1, R_L_HALF_FB.2, R_L_HALF_IN.2, U_L.6
L_LED_1_K: J_LINK_TOP.1, U_METER_L.2
L_LED_2_K: J_LINK_TOP.2, U_METER_L.1
L_LED_3_K: J_LINK_TOP.3, U_METER_L.14
L_LED_4_K: J_LINK_TOP.4, U_METER_L.13
L_N_SERIES: C_L_N_AC.1, R_L_N_SERIES.2
L_OUT: J_LINK_BOTTOM.3, R_L_ABS_RAW.1, R_L_HALF_IN.1, R_L_OUT.2, R_L_OUT_BLEED.1
L_PEAK_DRIVE: D_L_PEAK.2, U_L.14
L_PEAK_FOLLOW: D_L_PEAK.1, R_L_ATTACK.1, U_L.13
L_P_SERIES: C_L_P_AC.1, R_L_P_SERIES.2
L_RING: J_IN_L.2, R_L_N_BLEED.1, R_L_N_SERIES.1
L_RX_N: C_L_N_AC.2, U_RX.4
L_RX_OUT: J_LINK_BOTTOM.1, U_RX.13
L_RX_P: C_L_P_AC.2, U_RX.2
L_TIP: J_IN_L.1, R_L_P_BLEED.1, R_L_P_SERIES.1
L_WIPER: J_LINK_BOTTOM.2, R_L_WIPER_FAIL.1, U_L.3
R_ABS: R_R_ABS_FB.1, U_R.8, U_R.12
R_ABS_SUM: R_R_ABS_FB.2, R_R_ABS_HALF.2, R_R_ABS_RAW.2, U_R.9
R_DRIVE: C_R_GAIN_F.1, R_R_GAIN_F.1, R_R_OUT.1, U_R.1
R_ENV: C_R_HOLD.1, R_R_ATTACK.2, R_R_RELEASE.1, U_ENV.5
R_ENV_BUF: U_ENV.6, U_ENV.7, U_METER_R.4, U_METER_R.6, U_METER_R.8, U_METER_R.10
R_GAIN_FB: C_R_GAIN_F.2, R_R_GAIN_F.2, R_R_GAIN_G.1, U_R.2
R_HALF: D_R_HALF_RECT.2, R_R_ABS_HALF.1, R_R_HALF_FB.1
R_HALF_DRIVE: D_R_HALF_CLAMP.2, D_R_HALF_RECT.1, U_R.7
R_HALF_SUM: D_R_HALF_CLAMP.1, R_R_HALF_FB.2, R_R_HALF_IN.2, U_R.6
R_LED_1_K: J_LINK_TOP.5, U_METER_R.2
R_LED_2_K: J_LINK_TOP.6, U_METER_R.1
R_LED_3_K: J_LINK_TOP.7, U_METER_R.14
R_LED_4_K: J_LINK_TOP.8, U_METER_R.13
R_N_SERIES: C_R_N_AC.1, R_R_N_SERIES.2
R_OUT: J_LINK_BOTTOM.6, R_R_ABS_RAW.1, R_R_HALF_IN.1, R_R_OUT.2, R_R_OUT_BLEED.1
R_PEAK_DRIVE: D_R_PEAK.2, U_R.14
R_PEAK_FOLLOW: D_R_PEAK.1, R_R_ATTACK.1, U_R.13
R_P_SERIES: C_R_P_AC.1, R_R_P_SERIES.2
R_RING: J_IN_R.2, R_R_N_BLEED.1, R_R_N_SERIES.1
R_RX_N: C_R_N_AC.2, U_RX.5
R_RX_OUT: J_LINK_BOTTOM.4, U_RX.8
R_RX_P: C_R_P_AC.2, U_RX.7
R_TIP: J_IN_R.1, R_R_P_BLEED.1, R_R_P_SERIES.1
R_WIPER: J_LINK_BOTTOM.5, R_R_WIPER_FAIL.1, U_R.3
TH_1: R_TH_BOTTOM_1.1, R_TH_TOP_1.2, U_METER_L.5, U_METER_R.5
TH_2: R_TH_BOTTOM_2.1, R_TH_TOP_2.2, U_METER_L.7, U_METER_R.7
TH_3: R_TH_BOTTOM_3.1, R_TH_TOP_3.2, U_METER_L.9, U_METER_R.9
TH_4: R_TH_BOTTOM_4.1, R_TH_TOP_4.2, U_METER_L.11, U_METER_R.11
VLED: J_LINK_BOTTOM.8, R_LED_SUPPLY.2
VN: C_BULK_N.2, C_ENV_N.2, C_L_VN.2, C_RX_N.2, C_R_VN.2, D_PWR_N.2, U_ENV.4, U_L.11, U_R.11, U_RX.14
VN_RAW: D_PWR_N.1, J_PWR.1, J_PWR.2
VP: C_BULK_P.1, C_ENV_P.1, C_L_CMP.1, C_L_VP.1, C_RX_P.1, C_R_CMP.1, C_R_VP.1, D_PWR_P.1, R_LED_SUPPLY.1, R_REFERENCE.1, U_ENV.8, U_L.4, U_METER_L.3, U_METER_R.3, U_R.4, U_RX.1
VP_RAW: D_PWR_P.2, J_PWR.9, J_PWR.10
VREF: R_REFERENCE.2, R_TH_TOP_1.1, R_TH_TOP_2.1, R_TH_TOP_3.1, R_TH_TOP_4.1, U_REF.1, U_REF.2
